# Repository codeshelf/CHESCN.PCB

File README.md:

# CHESCN.PCB
The repo for the CHESCN PCB/A

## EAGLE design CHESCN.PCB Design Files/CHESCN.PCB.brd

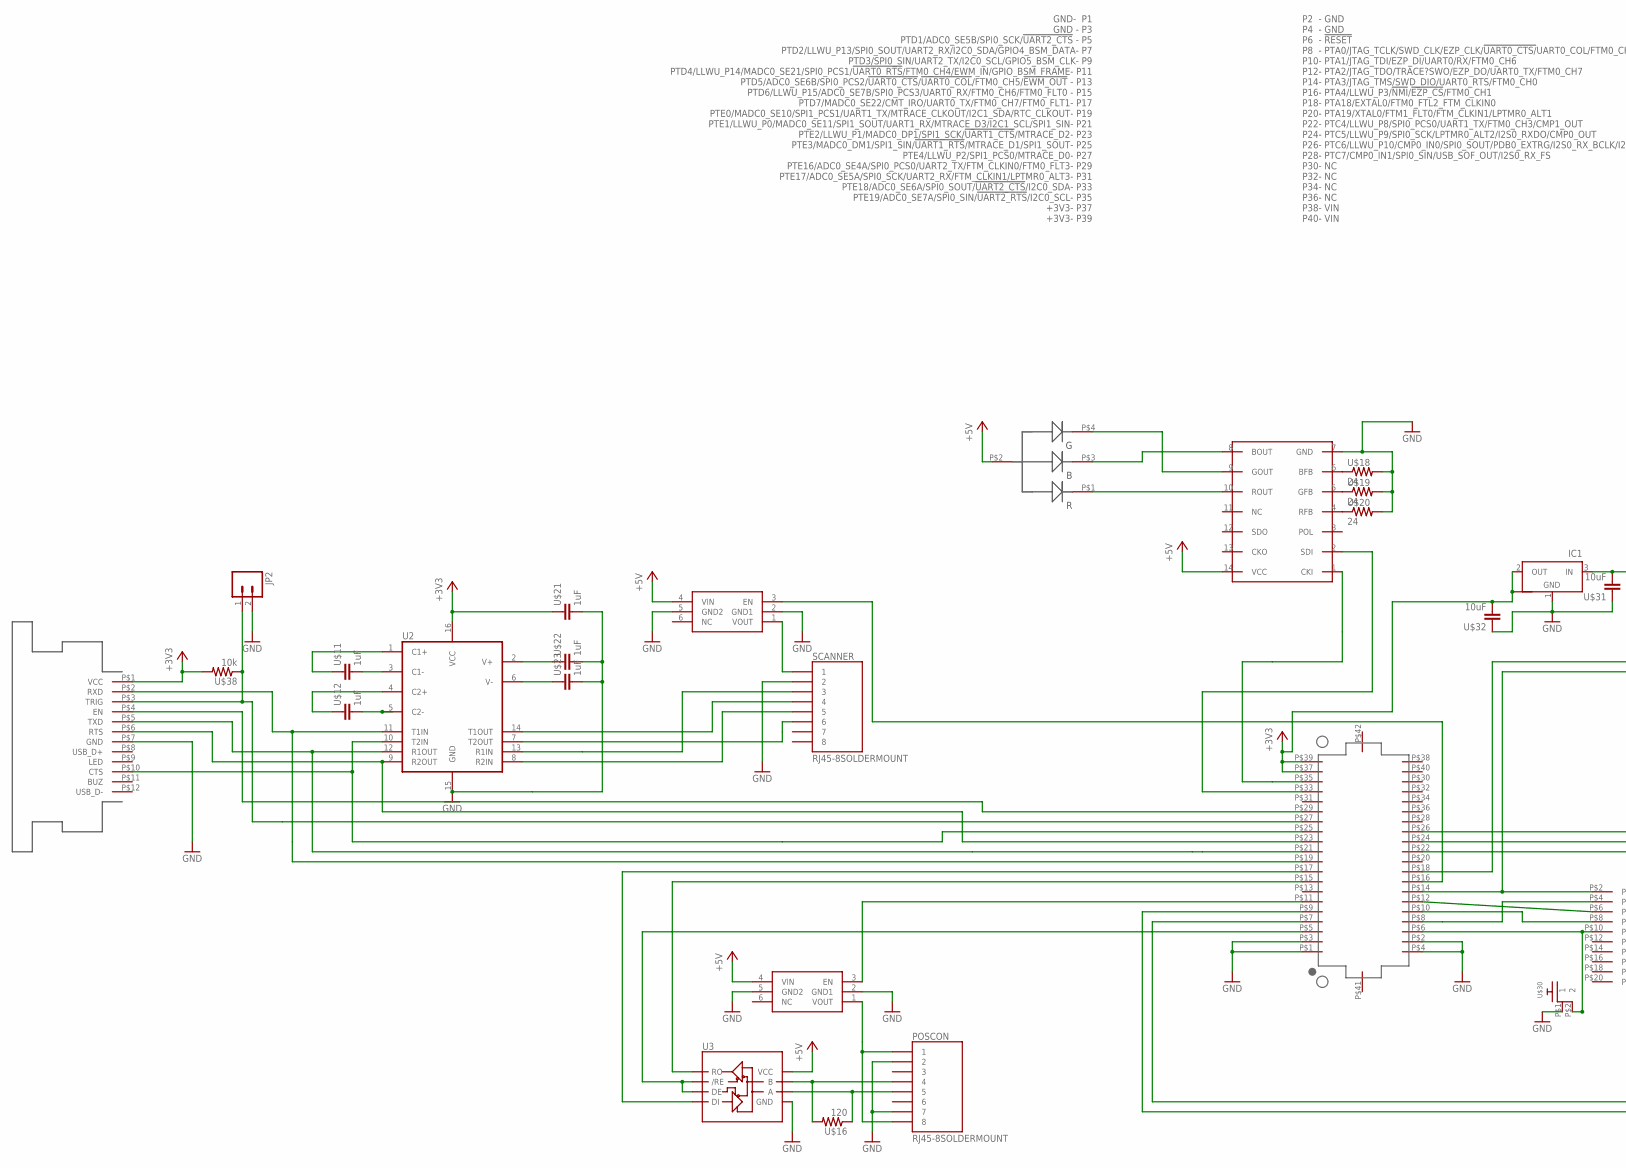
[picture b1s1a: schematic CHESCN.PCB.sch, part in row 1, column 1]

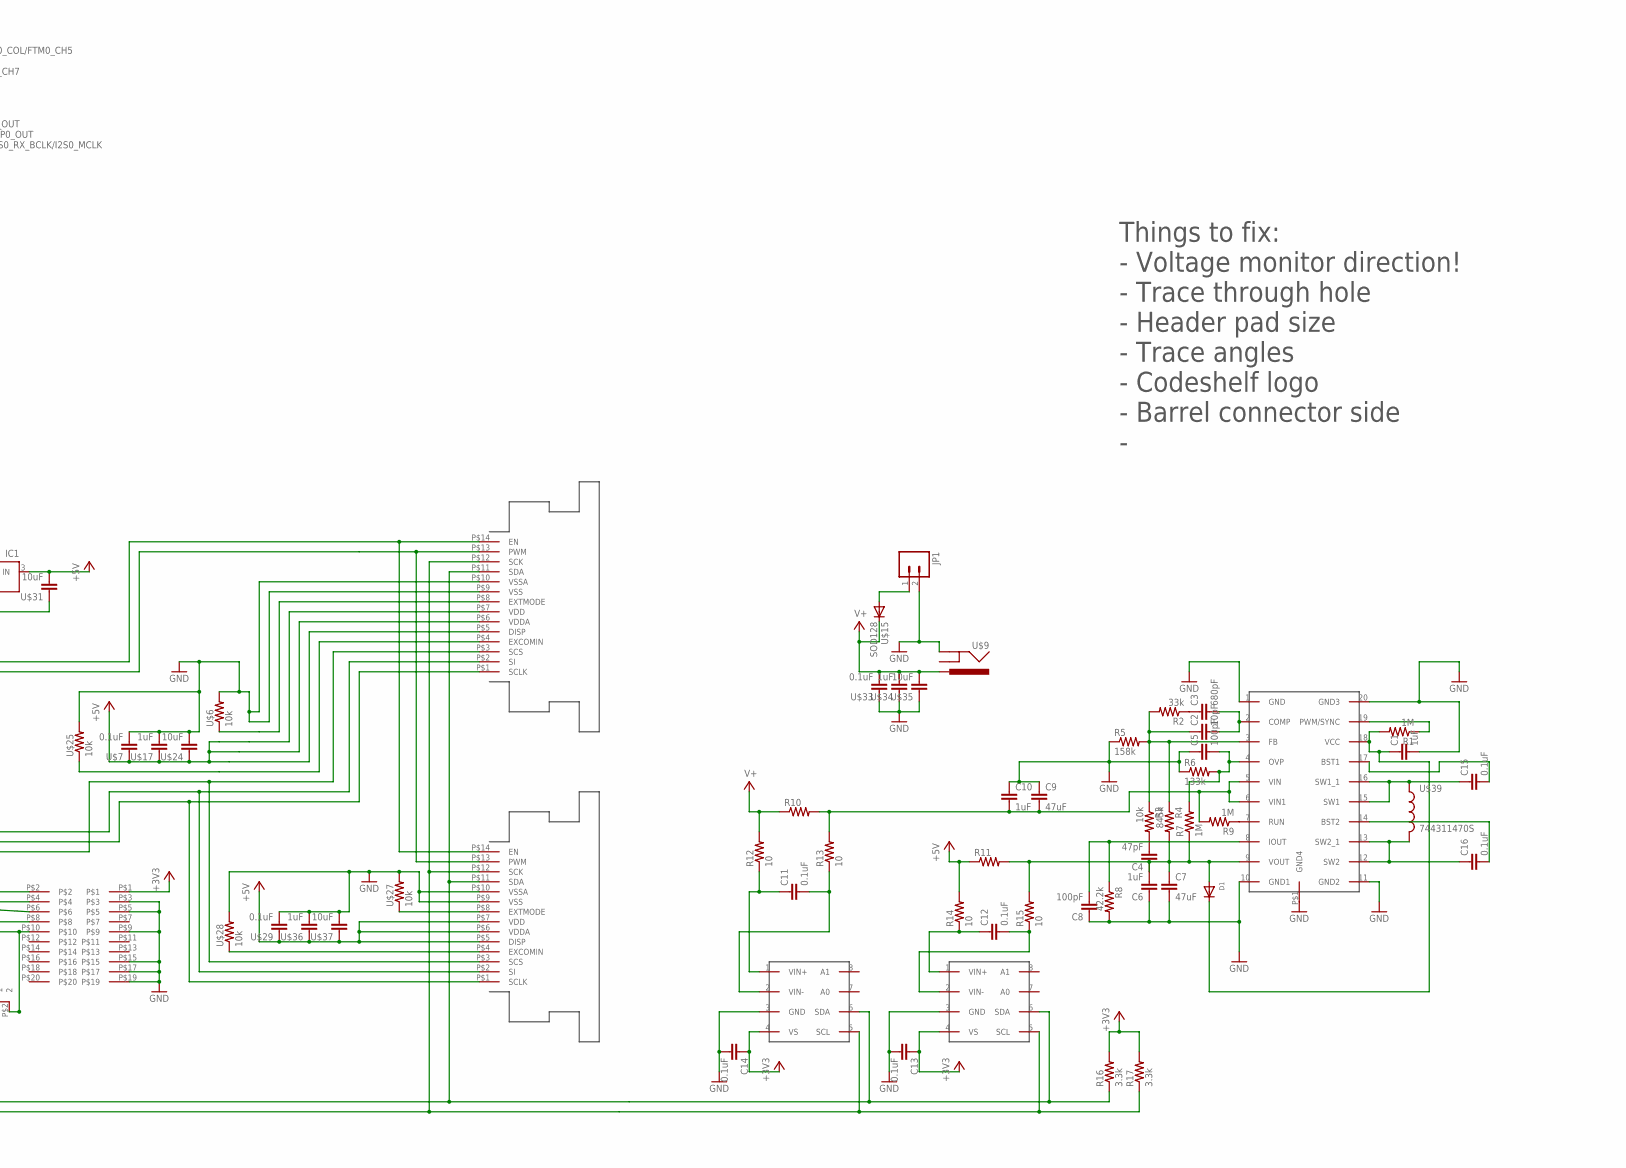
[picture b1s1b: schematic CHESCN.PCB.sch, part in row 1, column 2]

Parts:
C1, C6, C10: 1uF; C0603
C2: 10pF; C0402
C3: 680pF; C0402
C4: 47pF; C0402
C5, C8: 100pF; C0402
C7, C9: 47uF; C1210K
C11, C12, C13, C14, C15, C16: 0.1uF; C0402
D1: DIODESOD-123; SOD-123
IC1: NCP1117ST33T3G_1; SOT223
JP1, JP2: M02POGO_PIN_HOLES_ONLY; 1X02_PP_HOLES_ONLY
POSCON: RJ45-8SOLDERMOUNT; RJLSE4208101T
R1, R7, R9: 1M; RF-R0402
R2: 33k; RF-R0402
R3: 10k; RF-R0402
R4: 845k; RF-R0402
R5: 158k; RF-R0402
R6: 133k; RF-R0402
R8: 42.2k; RF-R0402
R10, R11: RF-R2512; R2512
R12, R13, R14, R15: 10; RF-R0402
R16, R17: 3.3k; RF-R0402
SCANNER: RJ45-8SOLDERMOUNT; RJLSE4208101T
U2: MAX232SOIC16; SO016
U3: RS485SOIC; SO08
U$1: RGLBED; RGBLED
U$2, U$14: SFV14R-2STE1HLF
U$3: 2X10JTAG
U$4, U$5: MIC94061C6; SC70-6L
U$6, U$25, U$27, U$28, U$38: 10k; RF-R0402
U$7, U$29, U$33: 0.1uF; C0402
U$8: WS2801; SO14
U$9: BARREL_CUI_PJ-002A
U$10: DF12_FOLD; BRAIN_OLD
U$11, U$12, U$17, U$21, U$22, U$23, U$34, U$36: 1uF; C0402
U$15: SOD128
U$16: 120; RF-R0402
U$18, U$19, U$20: 24; RF-R0402
U$24, U$31, U$32, U$35, U$37: 10uF; C0805
U$26: SFV12R-1STE1HLF
U$30: RA_BUTTON
U$39: 744311470S; IHLP4040DZ
U$44: LTC3112; TSSOP20
U$45, U$46: INA219B; DCN-R-PDSO-G8

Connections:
+3V3: C13.1, C14.1, IC1.2 (OUT), IC1.4 (OUT1), R16.2, R17.2, U2.16 (VCC), U$3.P$1, U$10.P$37 (+3V3), U$10.P$39 (+3V3), U$21.1, U$26.P$1 (VCC), U$32.2, U$38.2, U$45.4 (VS), U$46.4 (VS)
+5V: IC1.3 (IN), R11.1, R14.2, U3.8 (VCC), U$1.P$2 (ANODE), U$2.P$5 (DISP), U$2.P$6 (VDDA), U$2.P$7 (VDD), U$4.4 (VIN), U$5.4 (VIN), U$7.1, U$8.14 (VCC), U$14.P$5 (DISP), U$14.P$6 (VDDA), U$14.P$7 (VDD), U$17.1, U$24.1, U$29.1, U$31.2, U$36.1, U$37.1
C1: U2.1 (C1+), U$11.1
C2: U2.4 (C2+), U$12.1
GND: C1.2, C5.1, C6.1, C7.2, C8.1, C9.1, C10.1, C13.2, C14.2, IC1.1 (GND), JP1.2, JP2.2, POSCON.P$2 (2), POSCON.P$7 (7), R5.1, R6.1, R8.2, SCANNER.P$2 (2), U2.15 (GND), U3.5 (GND), U$2.P$9 (VSS), U$2.P$10 (VSSA), U$3.P$3, U$3.P$5, U$3.P$9, U$3.P$15, U$3.P$17, U$3.P$19, U$4.2 (GND1), U$4.5 (GND2), U$5.2 (GND1), U$5.5 (GND2), U$6.2, U$7.2, U$8.7 (GND), U$9.P$2 (GND), U$10.P$1 (GND), U$10.P$2 (GND), U$10.P$3 (GND), U$10.P$4 (GND), U$14.P$9 (VSS), U$14.P$10 (VSSA), U$17.2, U$18.2, U$19.2, U$20.2, U$21.2, U$22.2, U$23.2, U$24.2, U$25.2, U$26.P$7 (GND), U$27.2, U$28.2, U$29.2, U$30.P$1 (1), U$31.1, U$32.1, U$33.1, U$34.1, U$35.1, U$36.2, U$37.2, U$44.1 (GND), U$44.10 (GND1), U$44.11 (GND2), U$44.20 (GND3), U$44.P$1 (GND4), U$45.3 (GND), U$46.3 (GND)
unnamed: U$2.P$13 (PWM), U$3.P$2, U$10.P$14 (PTA3/JTAG_TMS/SWD_DIO/UART0_RTS/FTM0_CH0), U$14.P$13 (PWM)
unnamed: U$3.P$6, U$10.P$12 (PTA2/JTAG_TDO/TRACE?SWO/EZP_DO/UART0_TX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)
unnamed: U$3.P$8, U$10.P$10 (PTA1/JTAG_TDI/EZP_DI/UART0/RX/FTM0_CH6)
unnamed: U$3.P$4, U$10.P$8 (PTA0/JTAG_TCLK/SWD_CLK/EZP_CLK/!UART0_C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)
unnamed: U$1.P$4 (GREEN), U$8.9 (GOUT)
unnamed: U$3.P$10, U$10.P$6 (!RESET), U$30.P$2 (2)
unnamed: SCANNER.P$6 (6), U2.7 (T2OUT)
unnamed: U$1.P$3 (BLUE), U$8.8 (BOUT)
unnamed: U$1.P$1 (RED), U$8.10 (ROUT)
unnamed: U2.12 (R1OUT), U$10.P$21 (PTE1/LLWU_P0/MADC0_SE11/SPI1_SOUT/UART1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), U$26.P$5 (TXD)
unnamed: U$8.1 (CKI), U$10.P$35 (PTE19/ADC0_SE7A/SPI0_SIN/!UART2_RTS!/I2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)
unnamed: SCANNER.P$4 (4), U2.14 (T1OUT)
unnamed: U$8.6 (BFB), U$18.1
unnamed: U$8.5 (GFB), U$19.1
unnamed: U$8.4 (RFB), U$20.1
unnamed: U$8.2 (SDI), U$10.P$33 (PTE18/ADC0_SE6A/SPI0_SOUT/!UART2_CTS!/I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)
unnamed: U3.1 (RO), U$10.P$15 (PTD6/LLWU_P15/ADC0_SE7B/SPI0_PCS3/UART0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)
unnamed: U2.3 (C1-), U$11.2
unnamed: POSCON.P$4 (4), U3.7 (B), U$16.2
unnamed: POSCON.P$5 (5), U3.6 (A), U$16.1
unnamed: U2.5 (C2-), U$12.2
unnamed: U2.6 (V-), U$23.1
unnamed: U2.2 (V+), U$22.1
unnamed: POSCON.P$1 (1), POSCON.P$8 (8), U$5.1 (VOUT)
unnamed: SCANNER.P$1 (1), U$4.1 (VOUT)
unnamed: U2.11 (T1IN), U$10.P$19 (PTE0/MADC0_SE10/SPI1_PCS1/UART1_TX/MTRA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), U$26.P$2 (RXD)
unnamed: U3.4 (DI), U$10.P$17 (PTD7/MADC0_SE22/CMT_IRO/UART0_TX/FTM0_C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)
unnamed: U3.2 (/RE), U3.3 (DE), U$10.P$5 (PTD1/ADC0_SE5B/SPI0_SCK/!UART2_CTS)
unnamed: U$2.P$2 (SI), U$10.P$26 (PTC6/LLWU_P10/CMP0_IN0/SPI0_SOUT/PDB0_E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), U$14.P$2 (SI)
unnamed: U$2.P$1 (SCLK), U$10.P$24 (PTC5/LLWU_P8/SPI0_PCS0/UART1_TX/FTM0_CH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), U$14.P$1 (SCLK)
unnamed: U$2.P$3 (SCS), U$10.P$22 (PTC4/LLWU_P8/SPI0_PCS0/UART1_TX/FTM0_CH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), U$14.P$3 (SCS)
unnamed: C15.1, U$39.P$1 (1), U$44.15 (SW1), U$44.16 (SW1_1)
unnamed: U$2.P$4 (EXCOMIN), U$25.1
unnamed: U$2.P$8 (EXTMODE), U$6.1
unnamed: C16.1, U$39.P$2 (2), U$44.12 (SW2), U$44.13 (SW2_1)
unnamed: C16.2, U$44.14 (BST2)
unnamed: C15.2, U$44.17 (BST1)
unnamed: C2.2, C3.2, U$44.2 (COMP)
unnamed: U$5.3 (EN), U$10.P$11 (PTD4/LLWU_P14/MADC0_SE21/SPI0_PCS1/!UAR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)
unnamed: U$4.3 (EN), U$10.P$16 (PTA4/LLWU_P3/!NMI!/!EZP_CS!/FTM0_CH1)
unnamed: U2.10 (T2IN), U$10.P$25 (PTE3/MADC0_DM1/SPI1_SIN/!UART1_RTS!/MTR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), U$26.P$10 (CTS)
unnamed: C3.1, R2.1
unnamed: C1.1, D1.C, R1.2, U$44.18 (VCC)
unnamed: R1.1, U$44.19 (PWM/SYNC)
unnamed: C2.1, R2.2, R3.1, R4.1, R5.2, U$44.3 (FB)
unnamed: C4.2, R3.2
unnamed: C9.2, C10.2, R9.2, R10.2, R13.2, U$44.5 (VIN), U$44.6 (VIN1)
unnamed: C4.1, C6.2, C7.1, D1.A, R4.2, R7.1, R11.2, R15.2, U$44.9 (VOUT)
unnamed: C5.2, R6.2, R7.2, U$44.4 (OVP)
unnamed: R9.1, U$44.7 (RUN)
unnamed: C8.2, R8.1, U$44.8 (IOUT)
unnamed: SCANNER.P$5 (5), U2.8 (R2IN)
unnamed: C11.1, R12.1, U$45.1 (VIN+)
unnamed: U2.9 (R2OUT), U$10.P$23 (PTE2/LLWU_P1/MADC0_DP1/SPI1_SCK/!UART1_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), U$26.P$6 (RTS)
unnamed: C11.2, R13.1, U$45.2 (VIN-)
unnamed: C12.1, R14.1, U$46.1 (VIN+)
unnamed: C12.2, R15.1, U$46.2 (VIN-)
unnamed: R16.1, U$2.P$11 (SDA), U$10.P$7 (PTD2/LLWU_P13/SPI0_SOUT/UART2_RX/I2C0_S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), U$14.P$11 (SDA), U$45.6 (SDA), U$46.6 (SDA)
unnamed: R17.1, U$2.P$12 (SCK), U$10.P$9 (PTD3/SPI0_SIN/UART2_TX/I2C0_SCL/GPIO5_B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), U$14.P$12 (SCK), U$45.5 (SCL), U$46.5 (SCL)
unnamed: JP2.1, U$10.P$27 (PTE4/LLWU_P2/SPI1_PCS0/MTRACE_D0), U$26.P$3 (TRIG), U$38.1
unnamed: U$2.P$14 (EN), U$10.P$18 (PTA18/EXTAL0/FTM0_FTL2_FTM_CLKIN0), U$14.P$14 (EN)
unnamed: U$10.P$29 (PTE16/ADC0_SE4A/SPI0_PCS0/UART2_TX/FTM_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), U$26.P$4 (EN)
unnamed: U$14.P$4 (EXCOMIN), U$28.1
unnamed: U$14.P$8 (EXTMODE), U$27.1
unnamed: JP1.1, U$15.P$2 (A)
R1IN: SCANNER.P$3 (3), U2.13 (R1IN)
V+: R10.1, R12.2, U$9.P$1 (PWR), U$15.P$1 (C), U$33.2, U$34.2, U$35.2

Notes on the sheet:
Things to fix: - Voltage monitor direction! - Trace through hole - Header pad size - Trace angles - Codeshelf logo - Barrel connector side -

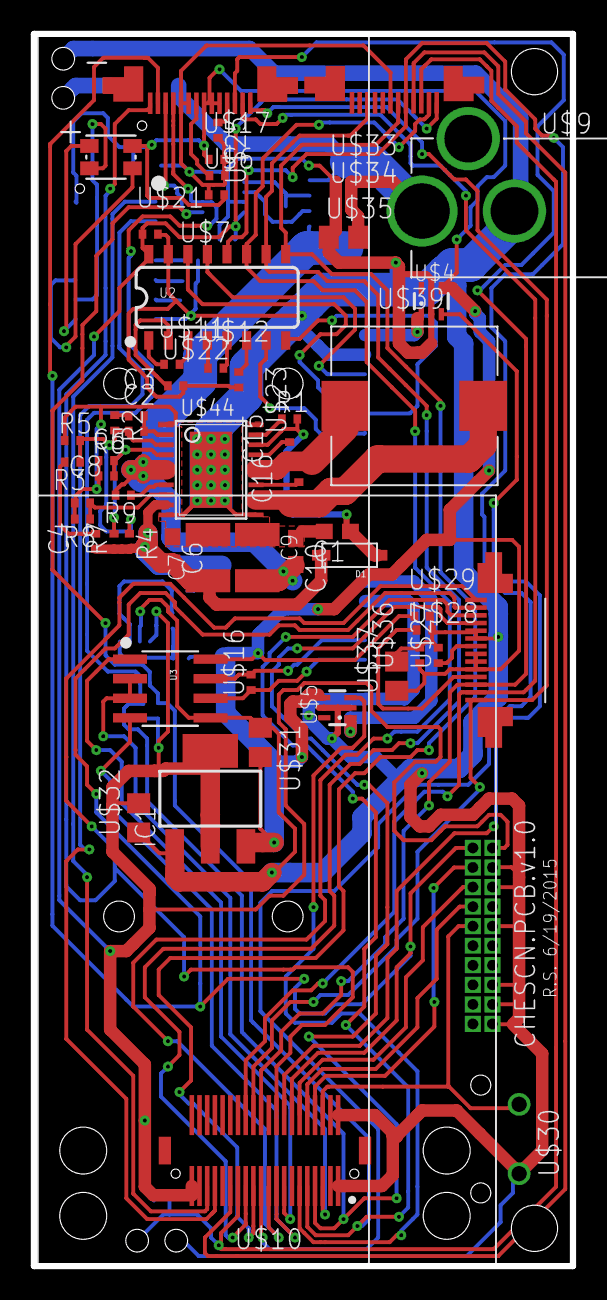
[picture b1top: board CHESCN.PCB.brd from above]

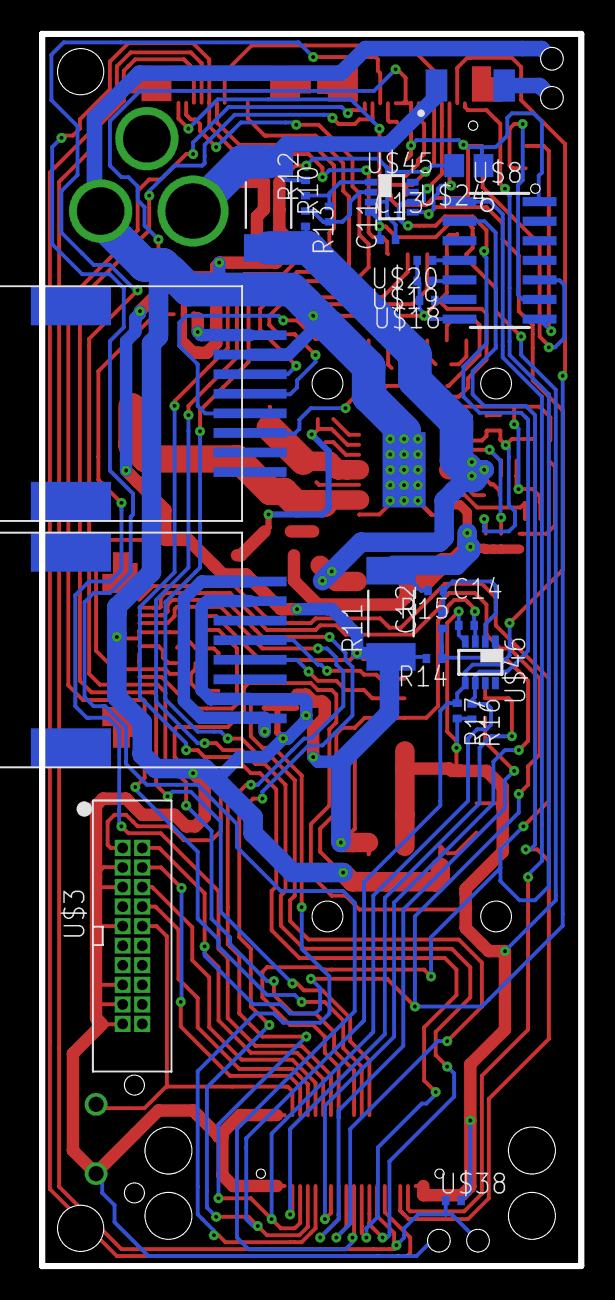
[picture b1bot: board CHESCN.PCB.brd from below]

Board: 2 copper layers, 35.0 x 80.0 mm, 83 parts (24 on the bottom side), 72 nets.

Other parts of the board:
U$13: 18650_1S1P

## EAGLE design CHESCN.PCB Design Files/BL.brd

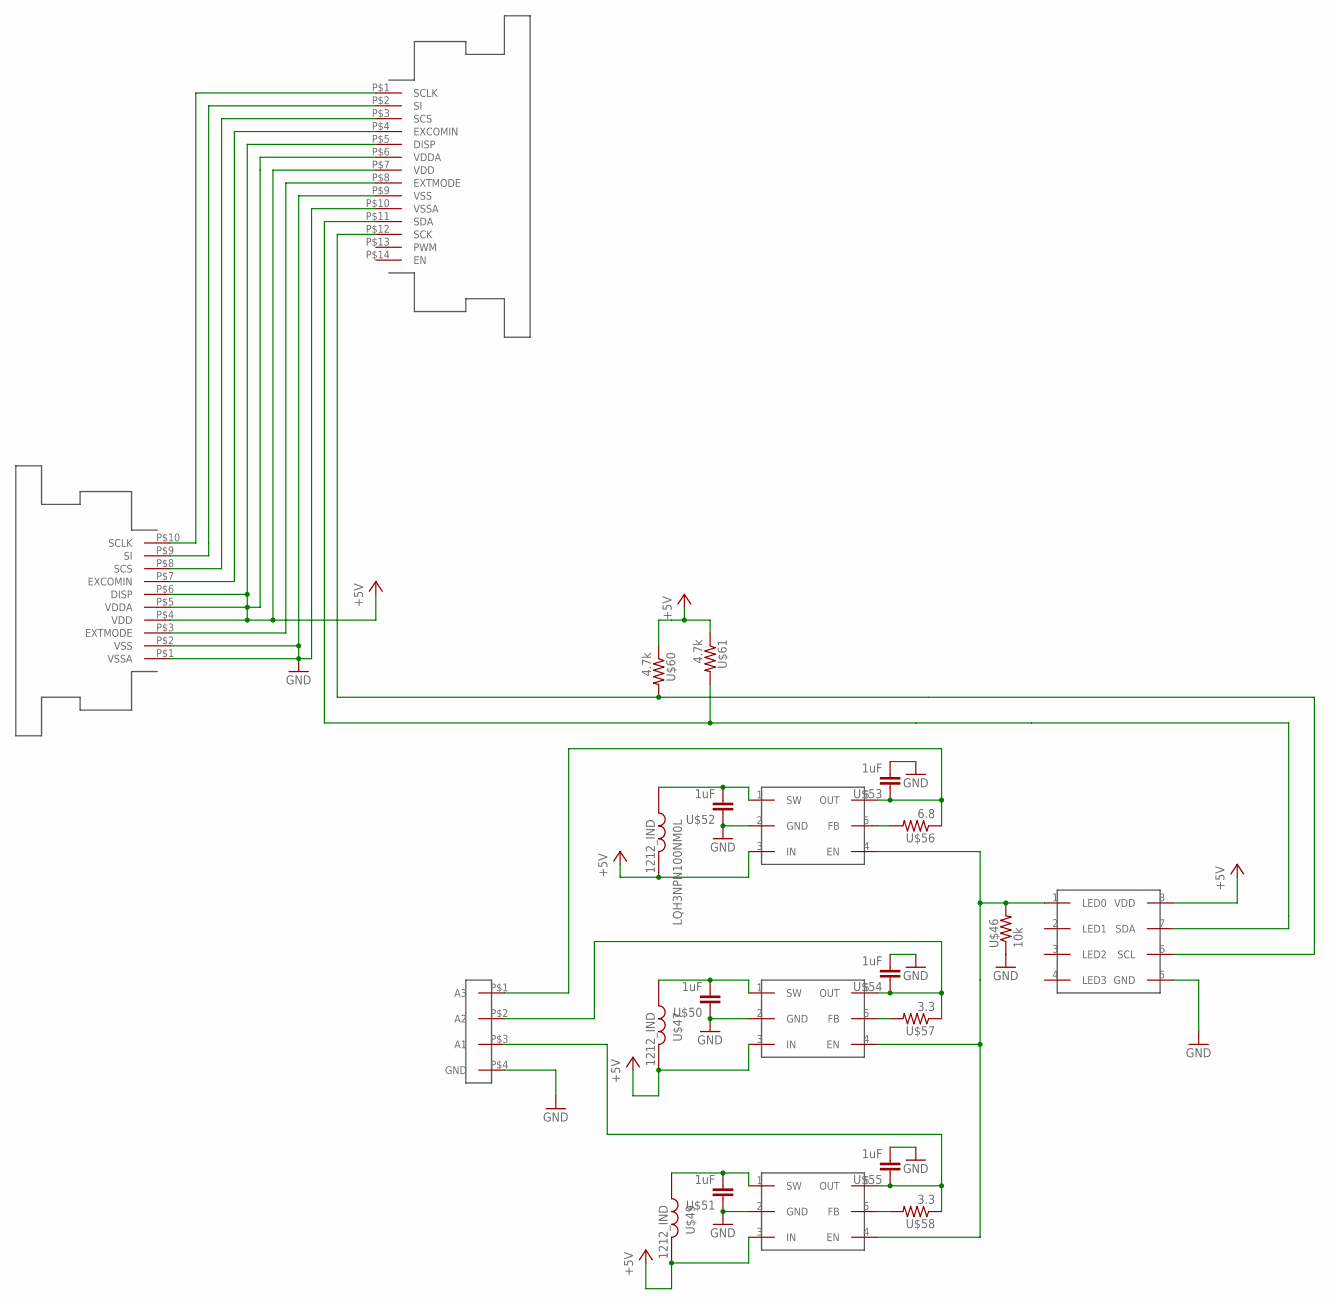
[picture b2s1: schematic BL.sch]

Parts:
LQH3NPN100NM0L: 1212_IND
U$1: 52745-1097
U$2: SFV14R-2STE1HLF
U$36, U$37, U$44: SC4541; SOT23-6
U$45: PCA9632DP1; TSSOP-8
U$46: 10k; RF-C0805
U$47, U$49: 1212_IND
U$50, U$51, U$52, U$53, U$54, U$55: 1uF; C0805
U$56: 6.8; RF-C0805
U$57, U$58: 3.3; RF-C0805
U$59: BL_CONSOLDER; S9091-46R
U$60, U$61: 4.7k; RF-C0805

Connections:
+5V: LQH3NPN100NM0L.P$1 (1), U$1.P$4 (VDD), U$1.P$5 (VDDA), U$1.P$6 (DISP), U$2.P$5 (DISP), U$2.P$6 (VDDA), U$2.P$7 (VDD), U$36.3 (IN), U$37.3 (IN), U$44.3 (IN), U$45.8 (VDD), U$47.P$1 (1), U$49.P$1 (1), U$60.1, U$61.1
GND: U$1.P$1 (VSSA), U$1.P$2 (VSS), U$2.P$9 (VSS), U$2.P$10 (VSSA), U$36.2 (GND), U$37.2 (GND), U$44.2 (GND), U$45.5 (GND), U$46.1, U$50.1, U$51.1, U$52.1, U$53.2, U$54.2, U$55.2, U$59.P$4 (GND)
unnamed: U$1.P$10 (SCLK), U$2.P$1 (SCLK)
unnamed: U$1.P$9 (SI), U$2.P$2 (SI)
unnamed: U$1.P$8 (SCS), U$2.P$3 (SCS)
unnamed: U$1.P$7 (EXCOMIN), U$2.P$4 (EXCOMIN)
unnamed: U$1.P$3 (EXTMODE), U$2.P$8 (EXTMODE)
unnamed: U$36.4 (EN), U$37.4 (EN), U$44.4 (EN), U$45.1 (LED0), U$46.2
unnamed: U$37.1 (SW), U$47.P$2 (2), U$50.2
unnamed: U$2.P$11 (SDA), U$45.7 (SDA), U$61.2
unnamed: LQH3NPN100NM0L.P$2 (2), U$36.1 (SW), U$52.2
unnamed: U$2.P$12 (SCK), U$45.6 (SCL), U$60.2
unnamed: U$44.1 (SW), U$49.P$2 (2), U$51.2
unnamed: U$44.5 (FB), U$58.2
unnamed: U$44.6 (OUT), U$55.1, U$58.1, U$59.P$3 (A1)
unnamed: U$37.5 (FB), U$57.2
unnamed: U$37.6 (OUT), U$54.1, U$57.1, U$59.P$2 (A2)
unnamed: U$36.6 (OUT), U$53.1, U$56.1, U$59.P$1 (A3)
unnamed: U$36.5 (FB), U$56.2

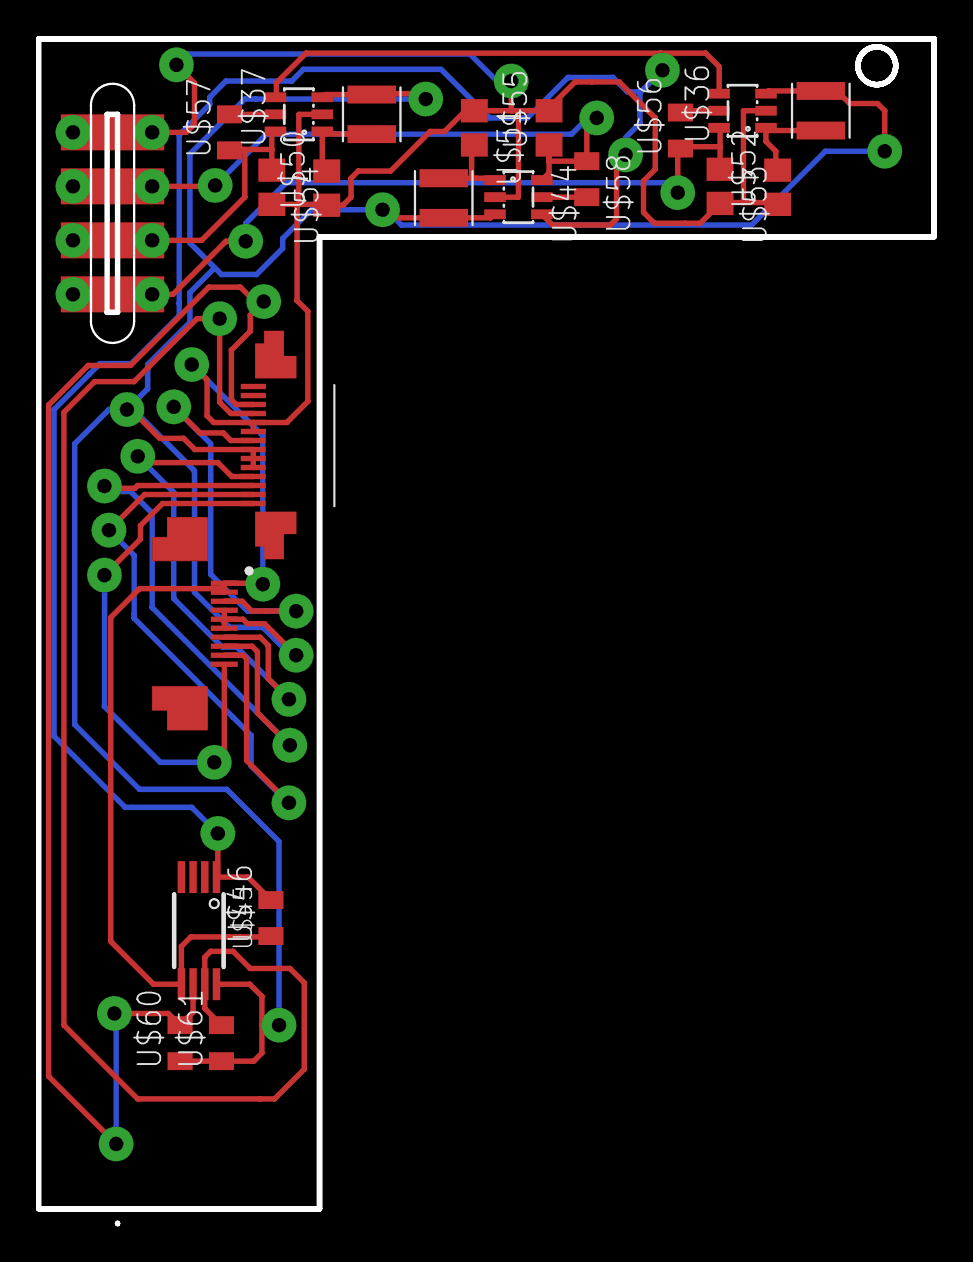
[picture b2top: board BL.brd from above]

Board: 2 copper layers, 49.7 x 65.8 mm, 22 parts (0 on the bottom side), 19 nets.

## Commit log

2015-05-27 Add initial source files
    Moved from local folder
2015-05-30 Still working on design..
    ..schematic almost complete.
2015-06-18 Routing complete
    Finished rounting. Requires 0.15mm milling and 0.25mm vias
2015-06-19 Pre-fab, added headers
    Need to export production files
2015-07-13 Various fixes + BL board
    Fixed consistency issues (diode, inductor), added laser test files and
    added backlight board
